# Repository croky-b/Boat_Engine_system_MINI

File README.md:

# Boat_Engine_system_MINI
Adaptation du projet de :https://github.com/TheDIYGuy999/Rc_Engine_Sound_ESP32 pour une utilisation "bateau"

Errata : Board Ver 1.6 : ESC1 et Led  4 partage la même Pin 19 

Il est possible de couper la piste en arriere de la resistance R10 et de relier un cable de R10 à D15 

une Nouvelle version 1.7 serra uploader

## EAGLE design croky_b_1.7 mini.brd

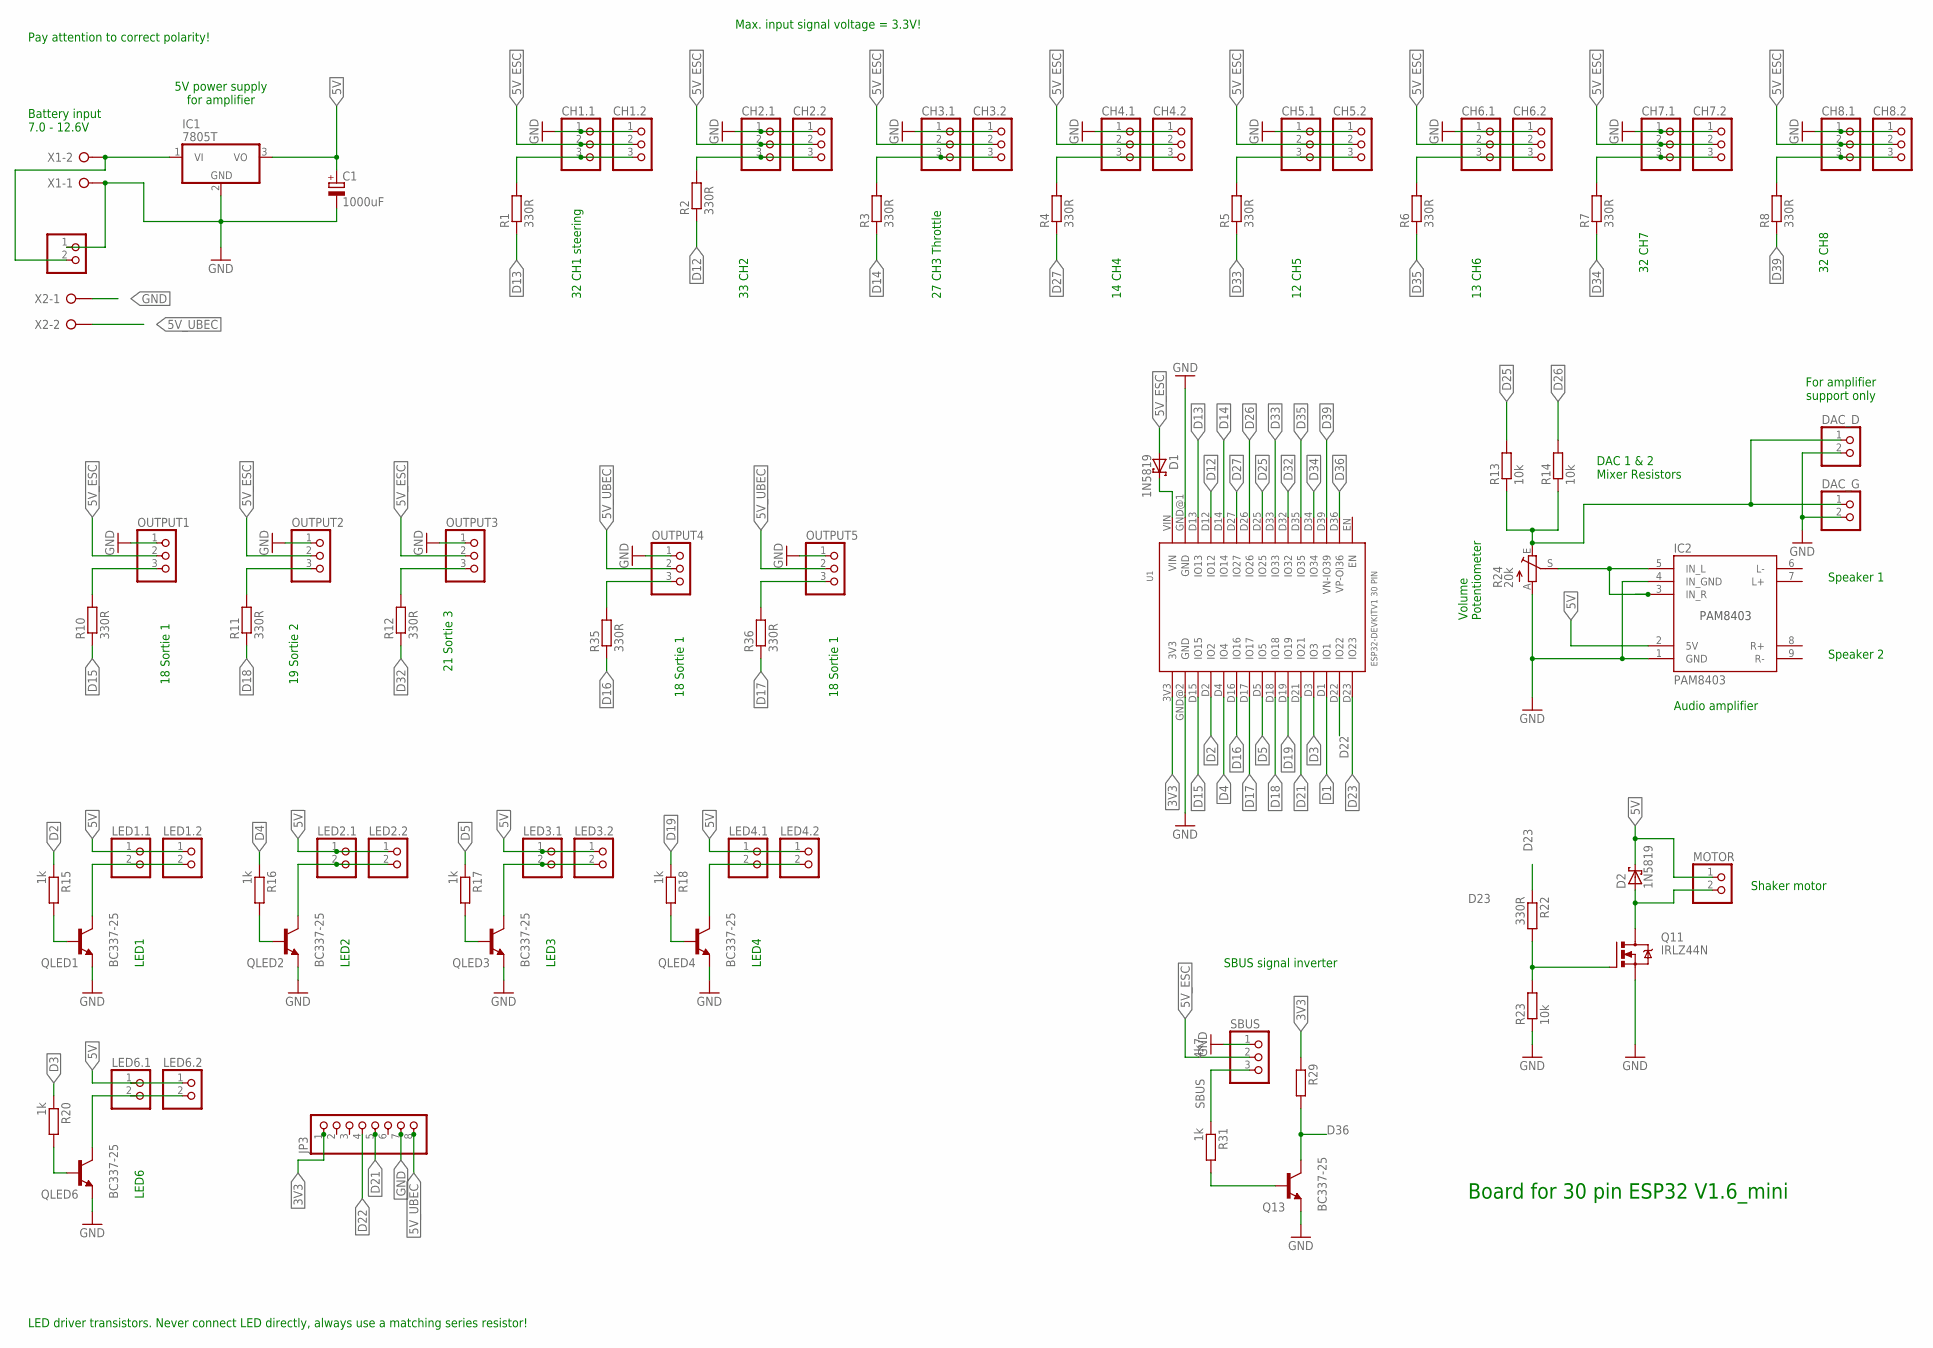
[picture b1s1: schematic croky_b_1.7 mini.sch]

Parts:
C1: 1000uF; E5-10,5
CH1.1, CH1.2, CH2.1, CH2.2, CH3.1, CH3.2, CH4.1, CH4.2, CH5.1, CH5.2, CH6.1, CH6.2, CH7.1, CH7.2, CH8.1, CH8.2: PINHD-1X3; 1X03
D1, D2: 1N5819; DO35-7
DAC_D: PINHD-1X2; 1X02
DAC_G: PINHD-1X2; 1X02
IC1: 7805T; TO220H
IC2: PAM8403
JP3: PINHD-1X8; 1X08
LED1.1, LED1.2, LED2.1, LED2.2, LED3.1, LED3.2, LED4.1, LED4.2, LED6.1, LED6.2: PINHD-1X2; 1X02
MOTOR, MOTOR2: PINHD-1X2; 1X02
OUTPUT1, OUTPUT2, OUTPUT3, OUTPUT4, OUTPUT5: PINHD-1X3; 1X03
Q11: IRLZ44N; TO220BV
Q13: BC337-25; TO92
QLED1, QLED2, QLED3, QLED4, QLED6: BC337-25; TO92
R1, R2, R3, R4, R5, R6, R7, R8, R10, R11, R12, R22, R35, R36: 330R; 0207/2V
R13, R14: 10k; 0207/10
R15, R16, R17, R18, R20, R31: 1k; 0207/2V
R23: 10k; 0207/2V
R24: 20k; S64W
R29: 4k7; 0207/2V
SBUS: PINHD-1X3; 1X03
U1: ESP32DEVKITV1; ESP32-DEVKITV1
X1, X2: W237-02P; W237-132

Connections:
3V3: JP3.1, R29.1, U1.3V3
5V: C1.+, D2.C, IC1.3 (VO), IC2.2 (5V), LED1.1.1, LED1.2.1, LED2.1.1, LED2.2.1, LED3.1.1, LED3.2.1, LED4.1.1, LED4.2.1, LED6.1.1, LED6.2.1, MOTOR.1
5V_ESC: CH1.1.2, CH1.2.2, CH2.1.2, CH2.2.2, CH3.1.2, CH3.2.2, CH4.1.2, CH4.2.2, CH5.1.2, CH5.2.2, CH6.1.2, CH6.2.2, CH7.1.2, CH7.2.2, CH8.1.2, CH8.2.2, D1.A, OUTPUT1.2, OUTPUT2.2, OUTPUT3.2, SBUS.2
5V_UBEC: JP3.8, OUTPUT4.2, OUTPUT5.2, X2.2
-: LED2.1.2, LED2.2.2, QLED2.3 (C)
--: LED3.1.2, LED3.2.2, QLED3.3 (C)
BAT+: IC1.1 (VI), MOTOR2.2, X1.2
D1: U1.D1 (IO1)
D2: R15.1, U1.D2 (IO2)
D3: R20.1, U1.D3 (IO3)
D4: R16.1, U1.D4 (IO4)
D5: R17.1, U1.D5 (IO5)
D12: R2.1, U1.D12 (IO12)
D13: R1.1, U1.D13 (IO13)
D14: R3.1, U1.D14 (IO14)
D15: R10.1, U1.D15 (IO15)
D16: R35.1, U1.D16 (IO16)
D17: R36.1, U1.D17 (IO17)
D18: R11.1, U1.D18 (IO18)
D19: R18.1, U1.D19 (IO19)
D21: JP3.5, U1.D21 (IO21)
D22: JP3.4, U1.D22 (IO22)
D23: R22.1, U1.D23 (IO23)
D25: R13.2, U1.D25 (IO25)
D26: R14.2, U1.D26 (IO26)
D27: R4.1, U1.D27 (IO27)
D32: R12.1, U1.D32 (IO32)
D33: R5.1, U1.D33 (IO33)
D34: R7.1, U1.D34 (IO34)
D35: R6.1, U1.D35 (IO35)
D36: Q13.3 (C), R29.2, U1.D36 (VP-OI36)
D39: R8.1, U1.D39 (VN-IO39)
GND: C1.-, CH1.1.1, CH1.2.1, CH2.1.1, CH2.2.1, CH3.1.1, CH3.2.1, CH4.1.1, CH4.2.1, CH5.1.1, CH5.2.1, CH6.1.1, CH6.2.1, CH7.1.1, CH7.2.1, CH8.1.1, CH8.2.1, DAC_D.2, DAC_G.2, IC1.2 (GND), IC2.1 (GND), IC2.4 (IN_GND), JP3.7, MOTOR2.1, OUTPUT1.1, OUTPUT2.1, OUTPUT3.1, OUTPUT4.1, OUTPUT5.1, Q11.S, Q13.1 (E), QLED1.1 (E), QLED2.1 (E), QLED3.1 (E), QLED4.1 (E), QLED6.1 (E), R23.1, R24.A, SBUS.1, U1.GND@1 (GND), U1.GND@2 (GND), X1.1, X2.1
unnamed: IC2.3 (IN_R), IC2.5 (IN_L), R24.S
unnamed: CH6.1.3, CH6.2.3, R6.2
unnamed: Q11.G, R22.2, R23.2
unnamed: CH5.1.3, CH5.2.3, R5.2
unnamed: CH4.1.3, CH4.2.3, R4.2
unnamed: CH7.1.3, CH7.2.3, R7.2
unnamed: CH3.1.3, CH3.2.3, R3.2
unnamed: D1.C, U1.VIN
unnamed: CH1.1.3, CH1.2.3, R1.2
unnamed: OUTPUT1.3, R10.2
unnamed: OUTPUT2.3, R11.2
unnamed: OUTPUT3.3, R12.2
unnamed: CH2.1.3, CH2.2.3, R2.2
unnamed: D2.A, MOTOR.2, Q11.D
unnamed: QLED1.2 (B), R15.2
unnamed: QLED6.2 (B), R20.2
unnamed: LED1.1.2, LED1.2.2, QLED1.3 (C)
unnamed: LED6.1.2, LED6.2.2, QLED6.3 (C)
unnamed: DAC_D.1, DAC_G.1, R13.1, R14.1, R24.E
unnamed: QLED3.2 (B), R17.2
unnamed: QLED2.2 (B), R16.2
unnamed: QLED4.2 (B), R18.2
unnamed: LED4.1.2, LED4.2.2, QLED4.3 (C)
unnamed: Q13.2 (B), R31.2
unnamed: CH8.1.3, CH8.2.3, R8.2
unnamed: OUTPUT4.3, R35.2
unnamed: OUTPUT5.3, R36.2
SBUS: R31.1, SBUS.3

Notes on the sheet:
Speaker 1
Speaker 2
13 CH6
12 CH5
14 CH4
27 CH3 Throttle
33 CH2
32 CH1 steering
18 Sortie 1
19 Sortie 2
21 Sortie 3
DAC 1 & 2 Mixer Resistors
Audio amplifier
Volume Potentiometer
5V power supply for amplifier
Battery input 7.0 - 12.6V
Board for 30 pin ESP32 V1.6_mini
Shaker motor
LED1
LED6
LED3
LED2
LED4
LED driver transistors. Never connect LED directly, always use a matching series resistor!
For amplifier support only
Pay attention to correct polarity!
Max. input signal voltage = 3.3V!
32 CH7
32 CH8
SBUS signal inverter

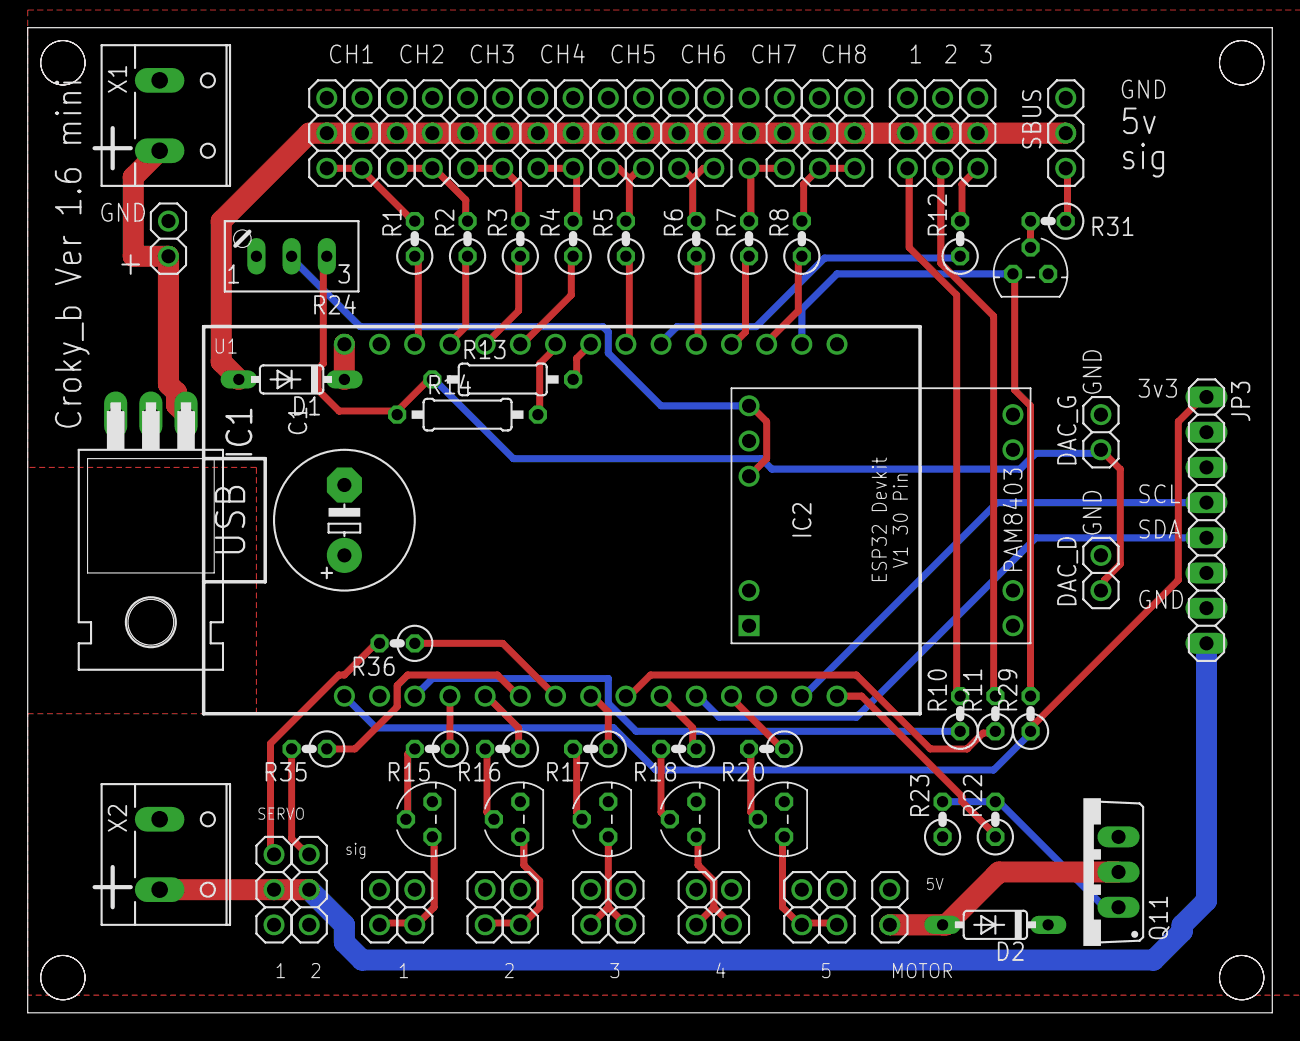
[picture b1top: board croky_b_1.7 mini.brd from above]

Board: 2 copper layers, 89.8 x 71.1 mm, 77 parts (1 on the bottom side), 60 nets.
